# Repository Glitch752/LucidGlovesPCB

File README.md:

# LucidGlovesPCB
A PCB for [LucidVR](https://github.com/LucidVR/lucidgloves) prototype 5 haptic gloves.

## Parts required
|Item                   |Link                                                                                     |Quantity required for 2 gloves|Quantity to purchase|Total price (as of writing)|Variant           |Notes                                                                      |
|-----------------------|-----------------------------------------------------------------------------------------|------------------------------|--------------------|---------------------------|------------------|---------------------------------------------------------------------------|
|49E Hall Effect Sensors|https://www.aliexpress.us/item/3256806022182106.html                                     |30                            |1                   |$5.28                      |50pcs             |3 per finger w/ splay                                                      |
|Neodymium magnets      |https://www.aliexpress.us/item/3256804031680743.html                                     |100                           |1                   |$2.44                      |100pcs            |Requires 5 per finger for flexion, +5 per finger for splay                 |
|Silicone Grips         |https://www.amazon.com/Protectors-Fingertips-Fingertip-Paperwork-Instrument/dp/B09P1SV9BM|10                            |1                   |$6.96                      |Pack of 50        |One per finger                                                             |
|Battery                |https://www.amazon.com/gp/product/B094G1GL8T                                             |2                             |1                   |$35.95                     |Pack of 2         |1 per hand; can use pretty much any USB power bank with two 2.1A outputs   |
|ESP-WROOM-32           |https://www.aliexpress.us/item/2251832678407407.html                                     |2                             |2                   |$5.66                      |ESP-WROOM-32D     |1 per hand                                                                 |
|MG90S Servo Motors     |https://www.aliexpress.us/item/3256805639785749.html                                     |10                            |1                   |$8.01                      |MG90S-10pcs       |5 per hand                                                                 |
|10x15x4mm Bearings     |https://www.aliexpress.us/item/3256802495161748.html                                     |20                            |2                   |$26                        |10pc 6700ZZ ABEC 1|2 per finger                                                               |
|CD74HC4067 Multiplexer |https://www.amazon.com/Ximimark-Digital-Multiplexer-Breakout-CD74HC4067/dp/B07K7JF3HX    |2                             |1                   |$6.99                      |Pack of 5         |1 per hand                                                                 |
|3D printed parts       |https://github.com/LucidVR/lucidgloves/wiki/Prototype-5-Beta-Printing-Guide              |2 sets                        |-                   |Depends                    |                  |                                                                           |

The total cost was $87.29 including batteries but excluding printed parts and the PCB as of writing.

You will also likely require:
- Solder and a soldering iron
- Dupont cables (or the connectors and a crimping kit to make your own for better cable management)
- Velcro (or an alternative way to secure the gloves)
- Foam (for comfort)
- Optionally some joysticks and buttons
- 4 short USB-C cables to attatch your batteries to the board if they don't come with some

## Images

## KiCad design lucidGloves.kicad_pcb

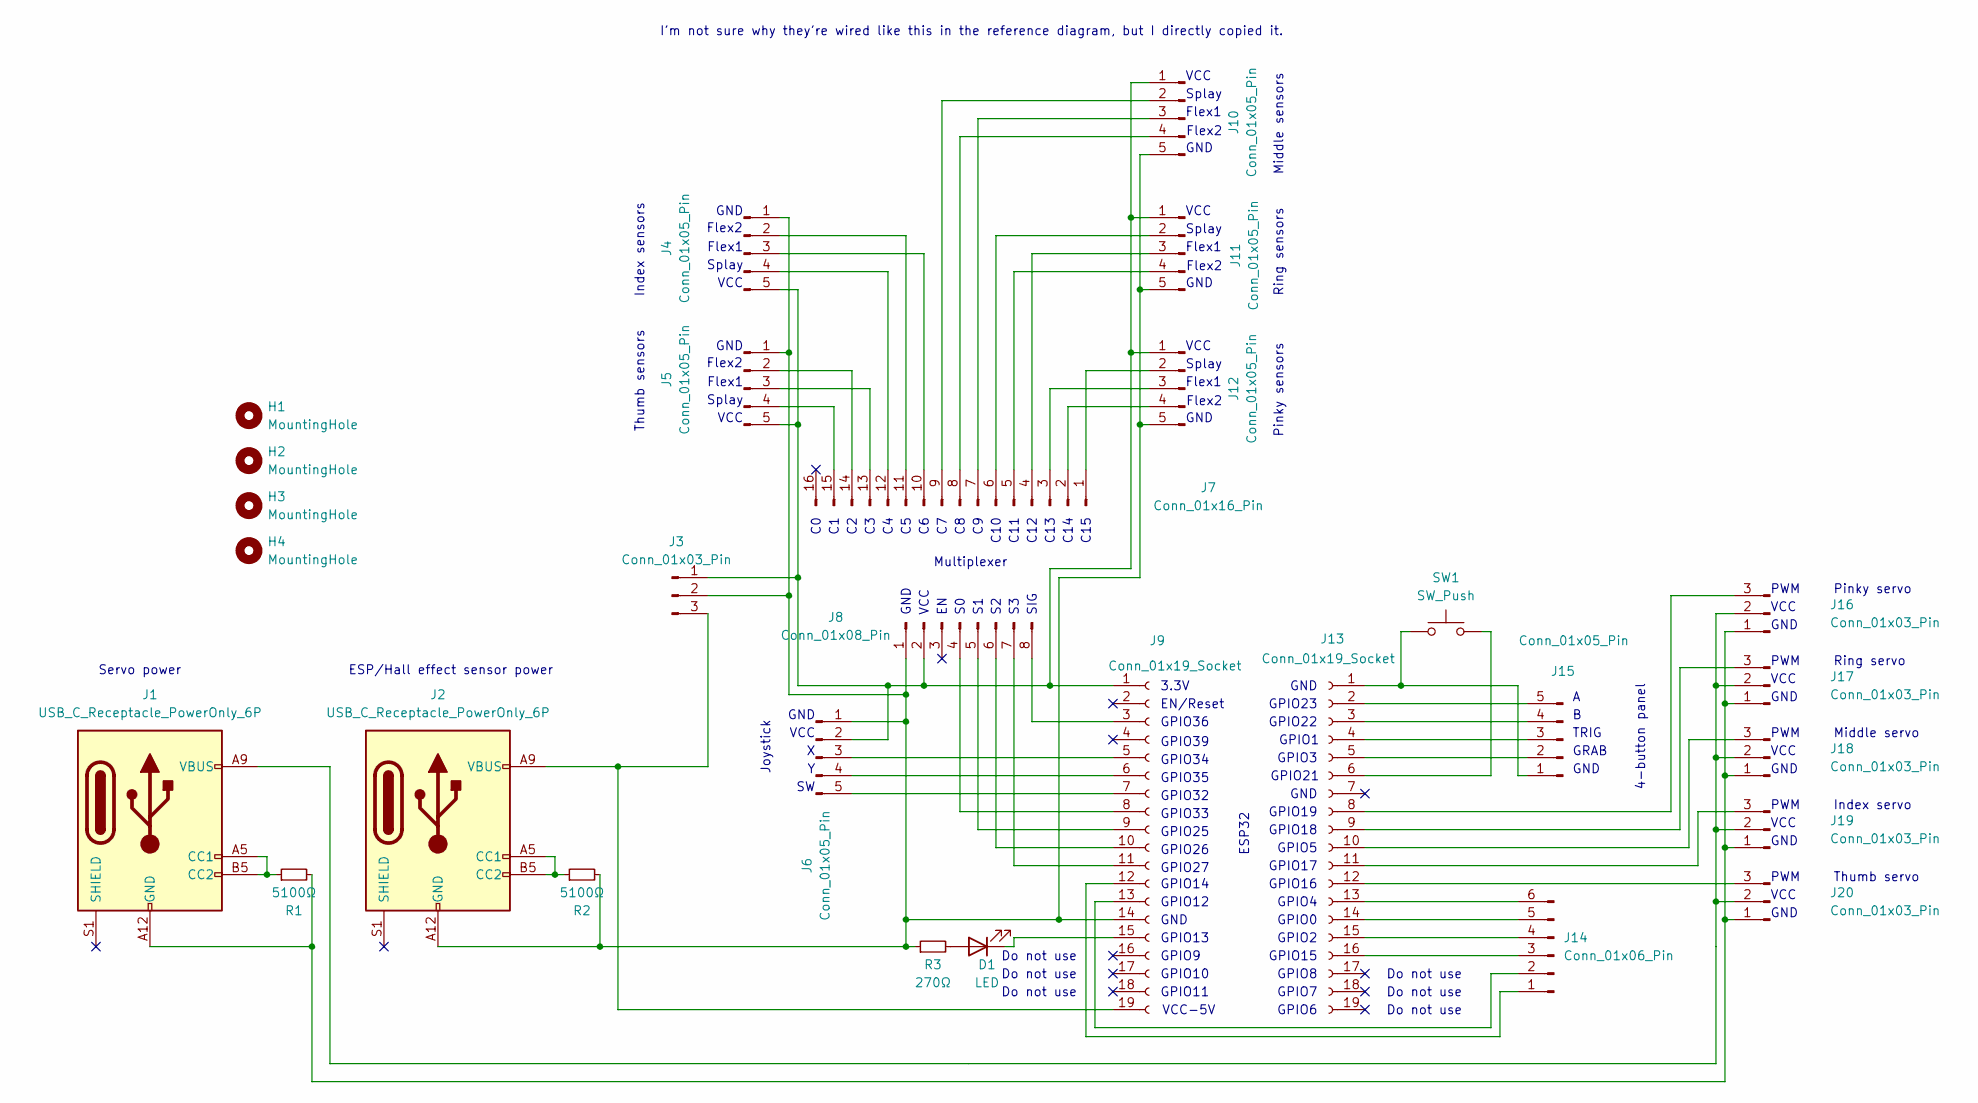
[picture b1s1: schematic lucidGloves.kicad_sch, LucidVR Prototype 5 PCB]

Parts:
D1: LED; LED_PLCC-2_3x2mm_AK; LCSC C2286
H1, H2, H3, H4: MountingHole; MountingHole_3.2mm_M3
J1, J2: USB_C_Receptacle_PowerOnly_6P; USB_C_Receptacle_GCT_USB4135-GF-A_6P_TopMnt_Horizontal; LCSC C2681548
J3: Conn_01x03_Pin; PinHeader_1x03_P2.54mm_Horizontal; LCSC C92159
J4, J5, J10, J11, J12: Conn_01x05_Pin; PinHeader_1x05_P2.54mm_Vertical; LCSC C5156614
J6, J15: Conn_01x05_Pin; PinHeader_1x05_P2.54mm_Horizontal; LCSC C138801
J7: Conn_01x16_Pin; PinHeader_1x16_P2.54mm_Vertical; LCSC C7501270
J8: Conn_01x08_Pin; PinHeader_1x08_P2.54mm_Vertical; LCSC C5156616
J9, J13: Conn_01x19_Socket; PinSocket_1x19_P2.54mm_Vertical; LCSC C319202
J14: Conn_01x06_Pin; PinHeader_1x06_P2.54mm_Horizontal; LCSC C56816
J16, J17, J18, J19, J20: Conn_01x03_Pin; PinHeader_1x03_P2.54mm_Vertical; LCSC C49257
R1, R2: 5100Ω; R_0402_1005Metric; LCSC C103079
R3: 270Ω; R_0402_1005Metric; LCSC C138294
SW1: SW_Push; SW_TH_Tactile_Omron_B3F-10xx; LCSC C271750

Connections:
unnamed: D1.2 (A), R3.2
unnamed: D1.1 (K), J9.15
unnamed: J1.A5 (CC1), J1.B5 (CC2), R1.1
unnamed: J2.A5 (CC1), J2.B5 (CC2), R2.1
unnamed: J2.A9 (VBUS), J2.B9 (VBUS), J3.3, J9.19
unnamed: J4.2, J7.11
unnamed: J4.3, J7.10
unnamed: J4.4, J7.12
unnamed: J5.2, J7.14
unnamed: J5.3, J7.13
unnamed: J5.4, J7.15
unnamed: J6.3, J9.5
unnamed: J6.4, J9.6
unnamed: J6.5, J9.7
unnamed: J8.4, J9.8
unnamed: J8.5, J9.9
unnamed: J8.6, J9.10
unnamed: J8.7, J9.11
unnamed: J8.8, J9.3
unnamed: J3.1, J4.5, J5.5, J6.2, J8.2, J9.1, J10.1, J11.1, J12.1
unnamed: J7.9, J10.2
unnamed: J7.7, J10.3
unnamed: J7.8, J10.4
unnamed: J2.A12 (GND), J2.B12 (GND), J3.2, J4.1, J5.1, J6.1, J8.1, J9.14, J10.5, J11.5, J12.5, R2.2, R3.1
unnamed: J7.6, J11.2
unnamed: J7.4, J11.3
unnamed: J7.5, J11.4
unnamed: J7.1, J12.2
unnamed: J7.3, J12.3
unnamed: J7.2, J12.4
unnamed: J13.1, J15.1, SW1.1
unnamed: J13.2, J15.5
unnamed: J13.3, J15.4
unnamed: J13.4, J15.3
unnamed: J13.5, J15.2
unnamed: J13.6, SW1.2
unnamed: J13.8, J16.3
unnamed: J13.9, J17.3
unnamed: J13.10, J18.3
unnamed: J13.11, J19.3
unnamed: J13.12, J20.3
unnamed: J13.13, J14.6
unnamed: J13.14, J14.5
unnamed: J13.15, J14.4
unnamed: J13.16, J14.3
unnamed: J9.12, J14.1
unnamed: J9.13, J14.2
unnamed: J1.A12 (GND), J1.B12 (GND), J16.1, J17.1, J18.1, J19.1, J20.1, R1.2
unnamed: J1.A9 (VBUS), J1.B9 (VBUS), J16.2, J17.2, J18.2, J19.2, J20.2

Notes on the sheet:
Flex1
GND
C15
SIG
GPIO14
Multiplexer
GPIO4
VCC
GPIO23
GPIO9
Pinky servo
Splay
GPIO39
GPIO34
GPIO35
GPIO26
Do not use
Flex2
GRAB
Index servo
GPIO10
VCC-5V
GPIO3
GPIO15
Servo power
Index sensors
GPIO12
GPIO27
ESP32
GPIO36
GPIO5
C10
GPIO13
GPIO1
GPIO16
GPIO2
C14
PWM
GPIO22
GPIO32

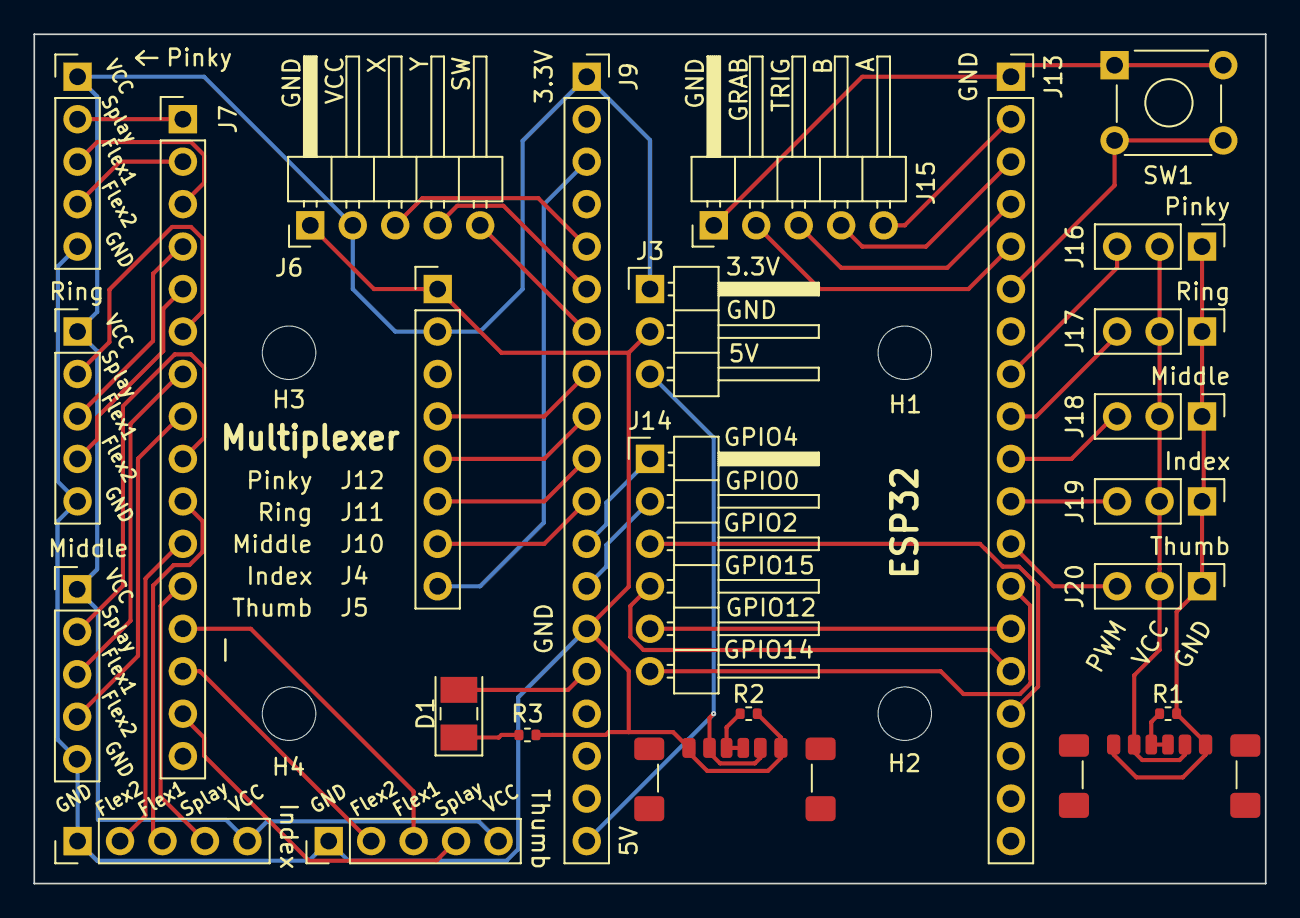
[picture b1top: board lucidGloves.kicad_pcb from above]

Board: 2 copper layers, 73.7 x 50.8 mm, 29 parts (0 on the bottom side), 49 nets.

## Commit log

2024-07-02 Initial project
2024-07-02 Change to KiCad 8, fix labels to be text elemnts
2024-07-02 Improve gitignore
2024-07-02 Fix all ERC errors and warnings
2024-07-02 Add footprints to schematic
2024-07-02 Mostly lay out PCB
2024-07-02 Correct PCB alignment and spacing
2024-07-02 Start routing wires and change USB C ports again
2024-07-03 Finish PCB
2024-07-03 Fix tiny placement issue
2024-07-03 Added servo/sensor labels and LucidVR logo
2024-07-03 Add gerber and drill files
2024-07-03 Many improvements and tweaks
2024-07-03 Tweaks for final JLCPCB order
2024-11-11 Fix multiplexer spacing
2024-11-19 Add part list CSV file
2024-11-19 Improve readme with parts list and images
